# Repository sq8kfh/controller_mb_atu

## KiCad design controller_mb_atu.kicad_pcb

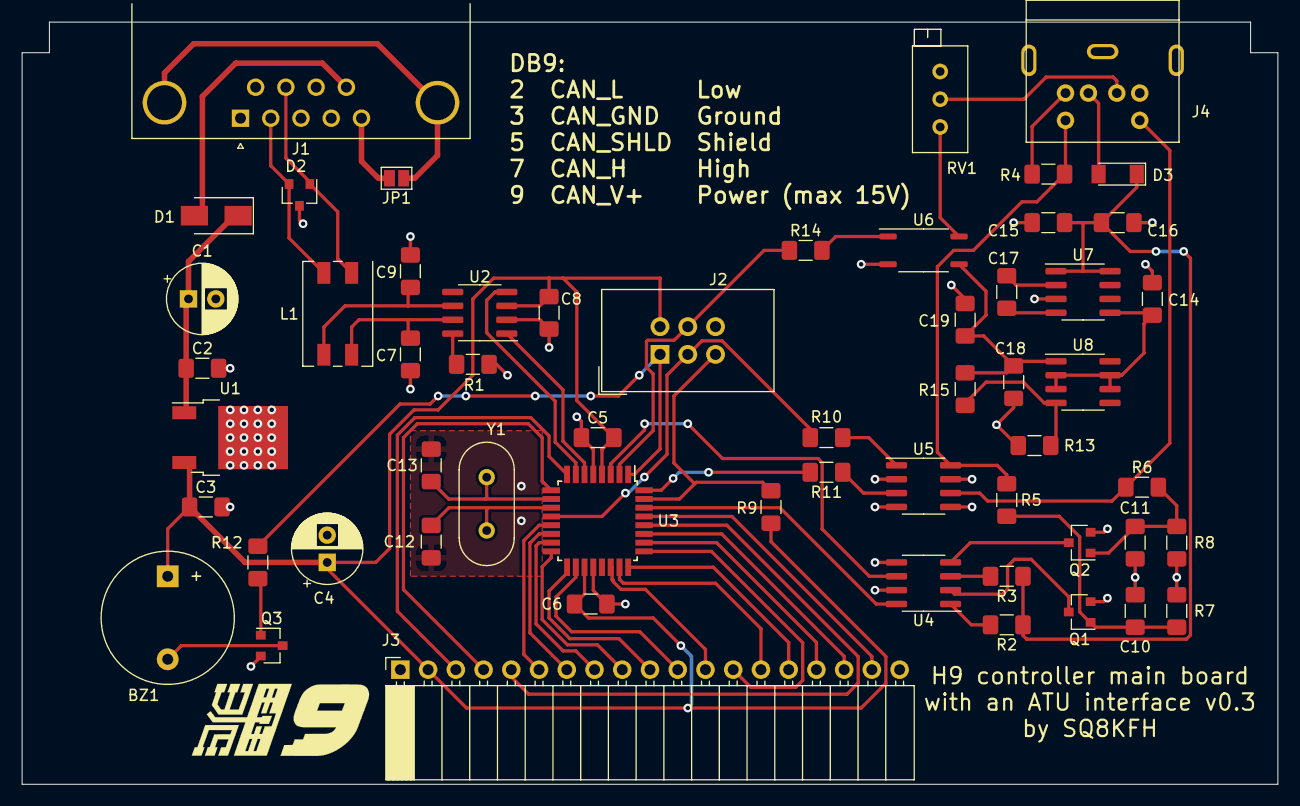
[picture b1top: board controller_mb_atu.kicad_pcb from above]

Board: 2 copper layers, 115.0 x 69.8 mm, 57 parts (0 on the bottom side), 62 nets.

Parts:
BZ1: Buzzer; Buzzer_12x9.5RM7.6
C1: 100uF; CP_Radial_D6.3mm_P2.50mm
C2, C3, C5, C6, C8, C16, C18: 100nF; C_1206_3216Metric_Pad1.42x1.75mm_HandSolder
C4: 47uF; CP_Radial_D6.3mm_P2.50mm
C7, C9: 47pF; C_1206_3216Metric_Pad1.42x1.75mm_HandSolder
C10, C11: 1nF; C_1206_3216Metric_Pad1.42x1.75mm_HandSolder
C12, C13: 22pF; C_1206_3216Metric_Pad1.42x1.75mm_HandSolder
C14, C17, C19: 1uF; C_1206_3216Metric_Pad1.42x1.75mm_HandSolder
C15: 4.7uF; C_1206_3216Metric_Pad1.42x1.75mm_HandSolder
D1: S1A; D_SMA
D2: NUP2105L; SOT-23
D3: 4148; D_MiniMELF
J1: CAN; DSUB-9_Female_Horizontal_P2.77x2.84mm_EdgePinOffset7.70mm_H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
J2: AVR-ISP-6; IDC-Header_2x03_P2.54mm_Vertical
J3: Front panel; PinSocket_1x19_P2.54mm_Horizontal
J4: Mini-DIN-6; LUMBERG_TM_0508_A6
JP1: Shield; SolderJumper-2_P1.3mm_Open_Pad1.0x1.5mm
L1: DR331-513AE; Filter_Bourns_SRF0905_6.0x9.2mm
Q1, Q2: 2N7002; SOT-23
Q3: BC817; SOT-23
R1: 39k; R_1206_3216Metric_Pad1.42x1.75mm_HandSolder
R2: 1k 0.25W; R_1206_3216Metric_Pad1.42x1.75mm_HandSolder
R3: 1k 0,25W; R_1206_3216Metric_Pad1.42x1.75mm_HandSolder
R4, R9: 10k; R_1206_3216Metric_Pad1.42x1.75mm_HandSolder
R5, R6: 10R; R_1206_3216Metric_Pad1.42x1.75mm_HandSolder
R7, R8: 100k; R_1206_3216Metric_Pad1.42x1.75mm_HandSolder
R10, R11, R12, R14: 390R; R_1206_3216Metric_Pad1.42x1.75mm_HandSolder
R13: 820R; R_1206_3216Metric_Pad1.42x1.75mm_HandSolder
R15: 240R; R_1206_3216Metric_Pad1.42x1.75mm_HandSolder
RV1: 20k; Potentiometer_Bourns_3296X_Horizontal
U1: LM78M05; TO-252-2
U2: MCP2551-I-SN; SOIC-8_3.9x4.9mm_P1.27mm
U3: ATmega32M1-AU; TQFP-32_7x7mm_P0.8mm
U4, U5: ILD213T; SOIC-8_3.9x4.9mm_P1.27mm
U6: TLP185(GR-TPL,E(O; SOIC-4_4.55x3.7mm_P2.54mm
U7: TC7662Bx0A; SOIC-8_3.9x4.9mm_P1.27mm
U8: LM337; SOIC-8_3.9x4.9mm_P1.27mm
Y1: 12MHz; Crystal_HC49-U_Vertical

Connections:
+5V: BZ1.1 (-), C3.1, C4.1, C5.2, C6.1, C8.2, J2.2 (VCC), J3.2, R9.1, U1.3 (VO), U2.3 (VDD), U3.4 (VCC), U3.19 (AVCC)
/ALC: J4.1, RV1.2
/CAN_H: D2.1 (K), J1.7, L1.1
/CAN_L: D2.2 (K), J1.2, L1.2
/CAN_RX: U2.4 (RXD), U3.7 (PC3)
/CAN_TX: U2.1 (TXD), U3.6 (PC2)
/KEY_I: R11.2, U3.32 (PD1)
/KEY_O: U3.3 (PC1), U4.6
/KEY_TT: J4.5, R6.1, U5.6
/MISO(BUZ): J2.1 (MISO), R12.1, U3.1 (PD2)
/MOSI(ALC): J2.4 (MOSI), R14.1, U3.2 (PD3)
/PB0(MISO): J3.3, U3.8 (PB0)
/PB1(MOSI): J3.4, U3.9 (PB1)
/PB2(INT1): J3.9, U3.16 (PB2)
/PB3: J3.14, U3.23 (PB3)
/PB4: J3.15, U3.24 (PB4)
/PB5(INT2): J3.16, U3.26 (PB5)
/PB6: J3.17, U3.27 (PB6)
/PB7(SCK): J3.5, U3.28 (PB7)
/PC4: J3.10, U3.17 (PC4)
/PC5: J3.11, U3.18 (PC5)
/PC6: J3.12, U3.22 (PC6)
/PC7(D2A): J3.13, U3.25 (PC7)
/PD0: J3.18, U3.29 (PD0)
/PD5: J3.6, U3.13 (PD5)
/PD6: J3.7, U3.14 (PD6)
/PD7: J3.8, U3.15 (PD7)
/PULLUP: J4.4, R4.2
/RST: J2.5 (~RST), R9.2, U3.31 (~RESET/PE0)
/SCK(START_I): J2.3 (SCK), R10.2, U3.12 (PD4)
/START_O: U3.30 (PC0), U4.8
/START_TS: J4.6, R4.1, R5.1, U5.8
GND: C1.2, C2.2, C3.2, C4.2, C5.1, C6.2, C7.1, C8.1, C9.2, C12.2, C13.2, D2.3 (A), J1.3, J2.6 (GND), J3.1, Q3.2 (E), R1.2, U1.2 (GND), U2.2 (VSS), U3.5 (GND), U3.20 (AGND), U4.5, U4.7, U5.2, U5.4, U6.3
GNDD: C10.2, C11.2, C14.1, C15.2, C16.2, C18.2, C19.2, J4.3, Q1.2 (S), Q2.2 (S), R7.1, R8.1, R13.1, RV1.3, U5.5, U5.7, U7.3 (GND)
unnamed: BZ1.2 (+), Q3.3 (C)
unnamed: C1.1, C2.1, D1.1 (K), U1.1 (VI)
unnamed: C9.1, L1.3, U2.6 (CANL)
unnamed: C10.1, Q1.1 (G), R5.2, R7.2
unnamed: C11.1, Q2.1 (G), R6.2, R8.2
unnamed: C12.1, U3.11 (XTAL2/PE2), Y1.1
unnamed: C13.1, U3.10 (XTAL1/PE1), Y1.2
unnamed: C14.2, U7.5 (VOUT), U8.2 (VI), U8.3 (VI), U8.6 (VI), U8.7 (VI)
unnamed: C15.1, C16.1, D3.1 (K), R2.1, R3.1, U7.1 (BOOST), U7.8 (V+)
unnamed: C17.1, U7.2 (CAP+)
unnamed: C17.2, U7.4 (CAP-)
unnamed: C18.1, C19.1, R15.2, U6.4, U8.1 (VO)
unnamed: D1.2 (A), J1.9
unnamed: D3.2 (A), J4.2
unnamed: J1.0 (PAD), JP1.1
unnamed: J1.5, JP1.2
unnamed: Q1.3 (D), U4.2
unnamed: Q2.3 (D), U4.4
unnamed: Q3.1 (B), R12.2
unnamed: R1.1, U2.8 (Rs)
unnamed: R2.2, U4.1
unnamed: R3.2, U4.3
unnamed: R10.1, U5.1
unnamed: R11.1, U5.3
unnamed: R13.2, R15.1, U8.4 (ADJ)
unnamed: R14.2, U6.1
unnamed: RV1.1, U6.6
unnamed: C7.2, L1.4, U2.7 (CANH)

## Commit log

2020-12-23 Init v0.1
2020-12-24 Add production files
2021-04-10 v0.2
2022-06-26 Add L1
